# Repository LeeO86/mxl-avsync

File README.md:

# mxl-avsync

AV sync and latency measurement for MXL, iPhone and Android. Version 2.2 uses a
large QR code beside two always-opposite light fields that swap in a short
burst at each event (AVS3), plus independently decodable audio timecode. File,
live MXL and the phone apps share the signal and measuring core. The analyzer
reports audio/video offset and, with a suitable clock reference, latency.
Phone-clock latency is an estimate; its physical accuracy depends on the
phone's camera and microphone (calibrate once per phone).

Part of [mxl-stack](https://github.com/LeeO86/mxl-stack), a collection of open-source MXL media functions with Docker Compose and Kubernetes examples.

Get `ghcr.io/leeo86/mxl-avsync:2.2.0` or see the [AVsync project site](https://leeo86.github.io/mxl-avsync/)
for iOS TestFlight information. Upgrade compact-signal generator and receivers
together: the picture QR is now AVS4 (it also carries the test ID, the
generator name and the sender calibration); AVS2/AVS3 generators and receivers
cannot read it, and AVS4 receivers ignore them. Legacy signals remain supported.
[Signal and validation details](docs/qr-flash.md) · [Release notes](docs/release-notes-2.2.0.md).

**Status: measuring core, file tools, control plane, live MXL reader and writer, and the phone core.** The container image is `ghcr.io/leeo86/mxl-avsync`, user 1000:1000. `/metrics` exports every family from the first scrape, counters at 0. Latency gauges are not exported. `mxl-avsync` links libmxl when the package is found; `avsync-core` does not. `/readyz` is 200 when the process and HTTP service are up and, with NMOS registration configured, the node is listed in the Query API. The generator also requires its output flows to be created. Analyzer routes and signal are independent: `not_routed`, `waiting` and `no_signal` remain ready and are reported in `/statusz`, the input-state metric and the UI. The analyzer also writes a result picture flow, and the web UI polls `/api/v1/preview/input.jpg` and `/api/v1/preview/generated.jpg` once a second. Clock state comes from an optional ptp4l management socket (`AVSYNC_PTP_SOCKET`), otherwise the kernel (`adjtimex(2)`); `AVSYNC_PTP_STATUS_URL` is an explicit override. `/statusz`, `/api/v1/status`, the UI and metrics identify `sync_source` (`ptp4l`, `kernel` or `url`). See [clock reference and deployment requirements](docs/clock-reference.md) for socket permissions, PTP error reporting and NTP TAI setup. Latency and the index shifts are reported only when that clock is locked and the QR names the event. Latency is arrival vs the content timestamp; directly behind the generator it is the generator's own write timing (both essences committed about 20–25 ms early, so negative). The main value is the AV sync, which is what MXL consumers see. For an absolute latency (emission → arrival, never negative, with ± and the clock named), enter the source's emit offsets on the analyzer (`AVSYNC_SOURCE_EMIT_VIDEO_MS` / `AVSYNC_SOURCE_EMIT_AUDIO_MS`, copied from the generator's `/api/v1/status` `emit_offsets`), or route the generator's flows directly with a Query API configured (the analyzer then reads the generator's flow tag `urn:x-mxl:tag:avsync-emit-offset-ms/v1.0`); without either the latency is relative to the source timestamp. Alert rules: `deploy/prometheus/avsync-rules.yaml`; per-release bench over several paths: `tools/bench_paths.py`. `video_content_vs_grain_ms` and `audio_content_vs_grain_ms` compare that content time with the MXL grain timestamp even when the clock is unknown. This repo does not implement ST 2110, SRT, or SIP; those flows come from the sibling gateways. File-mode H.264 and G.711 are test aids. A real phone still needs a device. Read [SPECIFICATION.md](SPECIFICATION.md), [IMPLEMENTATION_PLAN.md](IMPLEMENTATION_PLAN.md) and [docs/test-matrix.md](docs/test-matrix.md).

## Build

```bash
cmake -S . -B build -G Ninja -DCMAKE_BUILD_TYPE=Release
cmake --build build
./build/avsync-core-tests
./tests/integration/api.sh
./tests/integration/file.sh
./tests/integration/stage2.sh
node --test mobile-app/src/display.test.mjs
```

Needs CMake, Ninja, a C++20 compiler and the FFmpeg development libraries (libavformat, libavcodec, libavutil, libswscale, libswresample).

```bash
./build/mxl-avsync generate --format 1080p50 --duration 60 --offset 0 --out test.mov
./build/mxl-avsync analyze test.mov --manifest test.mov.manifest.json
AVSYNC_ROLE=generator AVSYNC_STATE_DIR=/tmp/avsync ./build/mxl-avsync serve
```

## At a glance

- C++20; one dependency-free core (`avsync-core`) shared by the CLI, the media function and the later phone app.
- `av_offset_ms = audio − video`: **positive = audio late**.
- Grade: pass −5…+15 ms (green), warn −40…+60 ms (orange, EBU R37), fail outside (red).
- CLI: `mxl-avsync generate` (MOV + ProRes + PCM by default, with a JSON manifest), `analyze`, `validate`, `merge`.
- Media function: one image, `AVSYNC_ROLE=generator` or `analyzer`; one measuring point (video + audio) per analyzer.
- Analyzer outputs: REST, WebSocket, `/metrics`, the `avsync` widget, a result video flow for the multiviewer, Grafana alert rules.
- Metrics (prefix `mxl_avsync_`, every family from the first scrape): grade, AV offset (gauge, histogram), events by result, input state, skipped input grains, resyncs, absolute latency per essence (`latency_abs_ms` and `latency_abs_uncertainty_ms` gauges: median over the grade window, NaN without a value; `latency_abs_seconds` histogram), `emit_offset_mismatch_total`, audio correlation and level, clock and PTP state; generator frames written/late/missed, `generator_render_seconds` and `generator_render_budget_seconds`. Full list: SPECIFICATION §16. Alert rules: `deploy/prometheus/avsync-rules.yaml`.
- NMOS IS-04/IS-05 with nmos-cpp when the build has it. Node label equals `NMOS_LABEL` verbatim (or `HOST_ID` when unset); the device label appends the role. Sender/receiver labels stay unchanged. DNS-SD is off unless `NMOS_DNS_SD=true`. Transport is `urn:x-nmos:transport:mxl`. An IS-05 receiver PATCH needs `transport_params` (`mxl_domain_id` and `mxl_flow_id`) from the sender's `/active`. A PATCH that carries only `sender_id` increments the activation counter and leaves the analyzer `not_routed`. `/livez`, `/readyz`, `/metrics`. The image `HEALTHCHECK` calls `/livez` on `WEB_PORT` (default 8180).
- Paths in this repo: file round trips, file-mode H.264 and G.711 as test aids, and MXL flows. The ST 2110 hour run goes through mxl-st2110-gateway. SRT and SIP/G.711 live inputs arrive as MXL flows from the sibling gateways. Stage 2 uses those gateways and tests the matrix; there is no transport code here. Phone app (Expo, iOS and Android) in 2.0.

## Ports

| Port | Setting | Default |
| --- | --- | --- |
| Web UI, REST, probes, metrics, widgets | `WEB_PORT` | 8180 |
| NMOS Node and Connection APIs | `NMOS_PORT` | 3332 (+1 reserved) |

## Exit codes

0 `--help`/`--version` (and a CLI run that completed), 75 a port or another startup failure, 78 invalid configuration, 143 SIGTERM/SIGINT. CLI `analyze`: 2 when no event was found.

## Licence

MIT (`LICENSE`).

## Ready-to-play test clips

See [testfiles/README.md](testfiles/README.md) for eight verified AV-sync clips in MP4, MOV and MKV (720p to 4K), known offsets, manifests, analysis reports and regeneration commands.

Signal and Settings forms keep local drafts across status/JPEG polling, with an Unsaved changes indicator and Apply/Discard. Only successful Apply or explicit Discard adopts the server settings; failed saves and newer edits made during a save are retained.

## Audio timecode and optical burst

The default signal carries independently decodable audio timecode at 1200 baud.
At zero offset, each optical burst starts with the chirp. Choose 1 or 2 chirps/s
in Signal; 600 baud and legacy compatibility are also available. See
[the format, phone feedback, audio-only latency and tests](docs/audio-timecode.md).

## Test-picture labels

The Signal form's **Title** is the large caption below the sync scale;
**Subtitle** is smaller. For existing deployments the saved `source` field and
`AVSYNC_SOURCE` keep their names and values. The obsolete header `title` /
`AVSYNC_TITLE` remains accepted by the legacy API but is not a second title
control for AVS3. Both container and phone show the centered AVsync brand.

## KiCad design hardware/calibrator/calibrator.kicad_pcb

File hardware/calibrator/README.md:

# AV Sync calibrator board

<!-- SPDX-License-Identifier: CERN-OHL-P-2.0 -->

**Status: v0.3 proposal, in development. Not ordered, not built, not tested.**

A small giveaway board (66 × 22 mm) for the AVsync app. The phone powers it over a
USB-C to USB-C cable. **No cable comes with the board: the user needs their own.**
It calibrates:

- **camera mode**: a phone's camera against its microphone (LED flash + click together),
- **display mode**: a sending screen against its speaker (the board clicks when the
  screen pattern swaps).

The board picks the mode from its two light sensors. What the app must do is in
[`docs/calibrator.md`](../../docs/calibrator.md). The firmware can be updated over the
same USB-C socket from a PC (see [Update over USB](#update-over-usb)).

Black solder mask, ENIG finish: the orange parts of the AVsync logo (waveform and the
ring in the middle) are bare gold copper; the rest of the logo is white silkscreen. The
bottom has a QR code to <https://leeo86.github.io/mxl-avsync/>.

Schematic: [`renders/calibrator-schematic.pdf`](renders/calibrator-schematic.pdf)
(also [SVG](renders/calibrator.svg)). 3D view: [`renders/calibrator-3d.png`](renders/calibrator-3d.png).

## How it works (short)

- **MCU**: WCH CH32X035G8R6 (RISC-V, QSOP-28). It runs straight from the phone's 5 V
  (2–5.5 V; 3.0–5.3 V while USB is used); 10 Ω + 1 µF/100 nF filter spikes. No regulator,
  no crystal.
- **USB-C, 16 pins**: 5.1 kΩ on CC1/CC2 so the phone turns on 5 V. D+/D− go to the MCU
  (PC17/PC16) **only for firmware updates**. The firmware never turns the USB block or its
  D+ pull-up on, so a phone sees no USB device: no "accessory not supported" message and
  no audio route change.
- **BOOT button** SW1 (update mode): connects D+ (PC17) to VDD through 4.7 kΩ (R9). The ROM bootloader
  starts only at power-on and only if PC17 is high then (CH32X035 datasheet, pin note 8).
- **Flash and click**: white LED (PA4, ~12 mA) and buzzer transistor (PA5) are on the same
  port, so one register write starts both.
- **Light sensors**: two phototransistors feed comparator 3 (PA13 +, PA2 −, hysteresis on).
  It flips at the crossing point of a black/white swap. 22 kΩ + 1 nF per sensor
  (τ ≈ 22 µs) delays that point by only ~15 µs, the same on both sensors. The ADC reads the same nodes (PA0,
  PA2) for dark/light and to check that a flip is real. PB3 is the comparator output
  (used inside the firmware) and must stay unconnected.

### Choices on the update path

- **No 10 kΩ pull-down on D+.** It was meant to stop a dumb wall charger (which may put
  ~2.7 V on D+) from starting the bootloader. That case is harmless (the board just waits
  in update mode until unplugged; the phone use case is not affected, because a phone holds
  D+ low with its own 15 kΩ). A pull-down would also fight the button: with the PC's 15 kΩ
  in parallel, D+ would only reach about 2.8 V when the button is pressed, too close to the
  unknown input threshold. Without it D+ reaches ~3.8 V with a PC attached and 5 V without.
- **R9 = 4.7 kΩ** (as on community CH32X035 boards) limits the current into D+ to well under
  1 mA while the button is held.
- **No ESD part on D+/D−.** USB is only used for the occasional update, the MCU pins have
  their own protection, and an extra extended part costs $3.07 per order plus ~$0.04/board
  (+$0.35/board on the 10-board test). Revisit if boards fail.

## Mechanics: why holes through the board

The LED must touch the camera lens and the sensors must lie flat on the screen, but the
buzzer (3 mm) and the USB-C receptacle (3.2 mm) are much taller than an LED.

| Option | Cost per order | Result |
| --- | --- | --- |
| **Chosen: all parts on top, LED and sensors look down through holes, bottom side flat** | 0 extra; sensors cost ~$0.40/board more than normal ones | flat bottom touches lens and screen; one-side Economic PCBA |
| Two-sided assembly (LED + sensors on the bottom) | Standard PCBA: setup $51.12 instead of $8.18, stencil $16.42, fixtures $41 (100 pcs), $0.48/board minimum | ≈ +$1.00/board at 100 |
| LED and sensors on the top, board lies parts-down | 0 | does not lie flat: buzzer and plug are 3 mm tall |

Parts that make the hole idea work, all in JLC stock:

- **LED**: XINGLIGHT XL-3216UWC-FB, a white *reverse-mount* 1206 LED. Its lens sits in a
  2.1 × 1.7 mm cut-out and shines through the board. Lite-On LTW-C230DS (C575513) fits the
  same footprint as a second source.
- **Sensors**: Vishay VEMT2500X01, a *reverse-gullwing* phototransistor (visible + IR,
  ±15°). The body sits on top, the dome lens looks down through a 2.3 mm hole. With a
  **1.2 mm board** the lens ends flush with the bottom. VEMT2000X01 is the same package.
- **USB-C at the far end**: the cable plug is thicker than the board and sticks out
  ~0.5 mm below the bottom. It sits ~55 mm away from the LED and sensors, so the board tilts
  less than 1° and the LED end stays flat on the lens or screen.

Look and markings:

- **Logo** on both sides, from `assets/app-icon.svg`: on the top centred in the free area
  between the BOOT button and the USB-C, on the bottom in the middle of the board, 11 mm,
  beside the QR code; the short instructions sit at the LED/sensor end. Cyan and white strokes are silkscreen.
  The orange parts are copper with a solder-mask opening and no paste, so with ENIG they look
  gold. That copper has no net; keep-outs keep tracks and vias away from it. Like in the
  icon, the white dashed centre line and the white centre dot lie on top of the gold: the
  copper and its mask opening are cut away under them, because JLC removes silkscreen from
  bare copper. On the bottom the logo and QR are mirrored so they read right from below.
- **QR code** (bottom): `https://leeo86.github.io/mxl-avsync/`. Version 3-M, 0.45 mm modules
  (3× JLC's 0.153 mm minimum line), 4-module quiet zone, white silkscreen on black mask
  (normal polarity), no via holes inside. Checked: zxing-cpp decodes the bottom render, also
  at 1/3 size. Matrix: `scripts/qr_matrix.txt` (from `scripts/gen_qr.py`, needs `segno`).
- **Text**: one font; name 1.8–2.0 mm, sub-lines 1.0–1.2 mm, and JLC's minimum
  (1.0 mm / 0.153 mm stroke) for "not a toy", the licence (small, below the MCU); "BOOT" under SW1 (1.2 mm bold).
- **Alignment**: LED circle, `A`/`B`, the split line (on the top next to the LED and again
  behind the buzzer, so it is visible while the board lies face down) and a half-round notch
  in the board edge on the split line. Marks on both sides.
- iPhone camera bumps: the lens rings stand higher than the bump plate. The board rests on
  the ring of the lens under the LED circle; hold it lightly or tape it. The buzzer sits
  next to the LED (5 mm), sound port pointing at the LED, close to the rear microphone.
- No company name on the board. Ground copper on both layers stops light going sideways
  through the board; no vias at the optics end.

## BOM (JLCPCB/LCSC, live stock and prices checked 2026-11-08)

USD per part at the order quantity of 10 and 100 boards. Ext = extended part
($3.07 feeder fee per type, Economic PCBA).

| Ref | Part | LCSC | Lib | Qty | Stock | $ @10 | $ @100 |
| --- | --- | --- | --- | --- | --- | --- | --- |
| U1 | CH32X035G8R6, QSOP-28 | C49118551 | Ext | 1 | 800 | 0.4351 | 0.3304 |
| Q2, Q3 | VEMT2500X01 phototransistor, reverse gullwing | C3210911 | Ext | 2 | 782 | 0.3141 | 0.2306 |
| BZ1 | MLT-8530 magnetic buzzer 8.5 × 8.5 × 3 mm | C94599 | Ext | 1 | 137,398 | 0.2015 | 0.158 |
| J1 | TYPE-C 16P receptacle (SHOU HAN), USB 2.0 | C393939 | Ext | 1 | 366,678 | 0.0691 | 0.0553 |
| D1 | XL-3216UWC-FB white LED, reverse mount | C3646935 | Ext | 1 | 111,067 | 0.0164 | 0.0164 |
| SW1 | TS-1187A tact switch 5.1 × 5.1 mm (update) | C318884 | Basic | 1 | 871,253 | 0.0207 | 0.0207 |
| Q1 | S8050 NPN, SOT-23 | C2146 | Basic | 1 | 1.45 M | 0.0141 | 0.0141 |
| D2 | 1N4148WS, SOD-323 | C2128 | Basic | 1 | 2.8 M | 0.011 | 0.011 |
| C1 | 10 µF 25 V 0805 | C15850 | Basic | 1 | 8.7 M | 0.0359 | 0.0359 |
| C2 | 1 µF 0402 | C52923 | Basic | 1 | 11.5 M | 0.0058 | 0.0058 |
| C3 | 100 nF 0402 | C1525 | Basic | 1 | 34.2 M | 0.0031 | 0.0031 |
| C4, C5 | 1 nF 0402 | C1523 | Basic | 2 | 2.3 M | 0.0038 | 0.0038 |
| R1, R2 | 5.1 kΩ 0402 | C25905 | Basic | 2 | 4.5 M | 0.0023 | 0.0023 |
| R3 | 10 Ω 0402 | C25077 | Basic | 1 | 3.6 M | 0.001 | 0.001 |
| R4 | 150 Ω 0603 | C22808 | Basic | 1 | 1.3 M | 0.0015 | 0.0015 |
| R5 | 1 kΩ 0402 | C11702 | Basic | 1 | 33.7 M | 0.0013 | 0.0013 |
| R6 | 100 kΩ 0402 | C25741 | Basic | 1 | 8.8 M | 0.0012 | 0.0012 |
| R7, R8 | 22 kΩ 0402 | C25768 | Basic | 2 | 1.0 M | 0.0012 | 0.0012 |
| R9 | 4.7 kΩ 0402 | C25900 | Basic | 1 | 15.7 M | 0.0017 | 0.0017 |

**Parts per board: $1.80 @10, $1.16 @100.** Stock covers the 10 + 100 boards (U1: 800,
sensors: 782 for 220 needed). Reserve them in the JLC parts library before ordering.

## Cost (both orders, CHF, everything included, no cables)

Assumptions: Economic PCBA fees from the JLC price page (setup $8.18, stencil $1.53,
5 extended types × $3.07, 95 joints × $0.0016, Confirm Parts Placement $0.45); PCB 2-layer
66 × 22 mm, 1.2 mm, **ENIG, black mask** [estimate: $21 for 10, $42 for 100; JLC's PCB price
only comes from their JavaScript calculator]; DHL $20 / $30 [estimate]; 1 USD = 0.80 CHF;
Swiss import VAT 8.1 % (only when ≥ CHF 5) + DHL clearance CHF 11.50 + 3 %.

| | Test, 10 boards | Run, 100 boards |
| --- | --- | --- |
| Parts | $18.0 | $116.0 |
| PCBA fees | $27.0 | $40.7 |
| PCB with ENIG + black | ~$21 | ~$42 |
| DHL | ~$20 | ~$30 |
| Subtotal | $86 → CHF 69 | $229 → CHF 183 |
| VAT 8.1 % + DHL clearance | CHF 5.6 + 11.7 | CHF 14.8 + 11.9 |
| **Total** | **≈ CHF 86 (CHF 8.60/board)** | **≈ CHF 210 (CHF 2.10/board)** |

**Both orders: ≈ CHF 296**, just under the CHF 300 budget. No programmer is needed (update
over USB-C). No cables are included. Ways to get more margin: JLC Global Standard Direct
instead of DHL (−CHF 10–20), or HASL instead of ENIG on the test batch (−~CHF 15; also stays
under the VAT limit). Run the real JLC quote with `fab/calibrator-gerbers.zip` before ordering.

## Update over USB

The CH32X035 has a USB bootloader in ROM, so the board cannot be bricked and needs no
programmer.

1. Unplug the board. Hold the **BOOT** button (SW1).
2. Plug the board into a PC (USB-C to USB-C, or USB-A to C). Release after about a second.
3. The board shows up as a WCH ISP device. Flash with an open tool:
   - [`wchisp`](https://github.com/ch32-rs/wchisp) (Rust, GPL-2.0): `wchisp flash firmware/build/calibrator.bin`
   - or `chprog.py` from [wagiminator/MCU-Flash-Tools](https://github.com/wagiminator/MCU-Flash-Tools) (MIT).
4. Unplug and plug in again: the new firmware runs.

A **blank chip** (as delivered by JLC) always starts the bootloader, so the first flash
needs no button. Linux needs a udev rule for the WCH device; see the
[firmware README](firmware/README.md). In normal use (no button) the phone never sees a
USB device.

## Files

| Path | What |
| --- | --- |
| `calibrator.kicad_pro/.kicad_sch/.kicad_pcb` | KiCad 9 project |
| `calibrator.kicad_sym` | custom CH32X035G8R6 symbol with pins grouped by use |
| `calibrator.pretty/` | custom footprints (buzzer, reverse LED, reverse-gullwing sensor) |
| `3d/` | simple box 3D models for the renders (KiCad 9's image has none for some parts; renders only, not used for assembly) |
| `fab/calibrator-gerbers.zip` | gerbers + drill for JLCPCB (order **1.2 mm**, **ENIG**, **black** mask, white silk) |
| `fab/calibrator-bom-jlc.csv`, `fab/calibrator-cpl-jlc.csv` | JLC BOM and pick-and-place files |
| `renders/` | PNG renders, schematic PDF/SVG |
| `scripts/` | generators: `design.py` (parts, nets, placement) → schematic (`gen_sch.py`, drawn in code), board (`gen_pcb.py`), fab files; `check_netlist.py` checks the drawn schematic against `design.py` |
| `firmware/` | CH32X035 firmware + host tests ([README](firmware/README.md)) |

### Rebuild

Needs docker only (pinned images `kicad/kicad:9.0.9-full`, `ghcr.io/freerouting/freerouting:2.1.0`).

```sh
scripts/build.sh   # footprints, schematic + netlist check, placement, autoroute, ground stitching, ERC, DRC
scripts/fab.sh     # gerbers, drill, BOM, CPL, renders, schematic PDF/SVG
```

The autorouter does not give the same tracks every run; the committed board is the
checked one.

### Checks

- ERC: 0 violations. Netlist check: the schematic wires give exactly the nets in `design.py`.
- DRC: 0 violations, 0 unconnected (JLC rules: 0.15 mm track/space, 0.3/0.6 mm vias,
  0.3 mm copper to board edge).
- Footprints match the datasheets (U1: QSOP-28 3.9 × 9.9 mm, 0.635 mm pitch, pin 1 top left;
  the USB-C uses KiCad's HRO TYPE-C-31-M-12 footprint, same pad layout as the SHOU HAN
  C393939 drawing).
- CPL rotations: JLC's 0° is the orientation of its own footprint for each part, which is
  not always KiCad's. `scripts/jlc_files.py` adds the known offsets for the stock footprints
  (QSOP-28 +270°, SOT-23 −90°, HRO USB-C +180°; values from the community list of JLC
  corrections, e.g. matthewlai/JLCKicadTools). Custom footprints (buzzer, reverse LED,
  sensors) and the button keep KiCad's rotation. Still check every part in JLC's placement
  preview before ordering (or use "Confirm Parts Placement"); JLC also places by the pin-1
  and polarity marks in the silkscreen.

## Risks and open points

1. **Phone powers the board?** A sink with 5.1 kΩ Rd is the standard USB-C way to ask for
   5 V. iPhone 15+ and most Android phones supply it. To test with real phones, including
   that no "accessory" message appears with D+/D− wired to the MCU.
2. **Bootloader entry**: R9/SW1 values follow community boards, not a WCH document; one
   user reports an "unknown device" when powered only from USB-C. Test on the first board.
3. **Comparator interrupt path** (comparator 3 → PB3 → EXTI) and the ADC/clock register
   setup are written from the datasheet, ch32fun and WCH EVT, not tested on hardware.
4. **Buzzer delay** from coil-on to sound is unknown (expect 0.05–0.3 ms). Measure once.
5. **Sensor signal** on dim screens (22 kΩ load) and room light entering the clear sensor
   bodies from above (both sensors alike, mostly cancels).
6. **LED fit**: the reverse LED lens (1.86 × 1.4 mm) has only ~0.1 mm room in the cut-out.
7. **Stock**: U1 800 and sensors 782 at JLC; enough for 110 boards, not for many more.
8. **VDD with USB**: the datasheet allows 3.0–5.3 V while USB runs; a PC port at the top of
   the USB range (5.25 V) is just inside.

## Licence

- **Board** (KiCad project, footprints, 3D models, scripts, fab files, renders and the logo
  artwork on the board): **CERN-OHL-P-2.0**, see
  [`LICENSE-CERN-OHL-P-2.0.txt`](LICENSE-CERN-OHL-P-2.0.txt).
  `SPDX-License-Identifier: CERN-OHL-P-2.0`. It is printed small on the top silkscreen.
  CERN-OHL-S-2.0 (share-alike: changed boards must stay open) would be the alternative.
- **Firmware** (`firmware/`): MIT, like the rest of the repository. Vendored register
  definitions come from ch32fun (MIT); see [`firmware/vendor/README.md`](firmware/vendor/README.md).

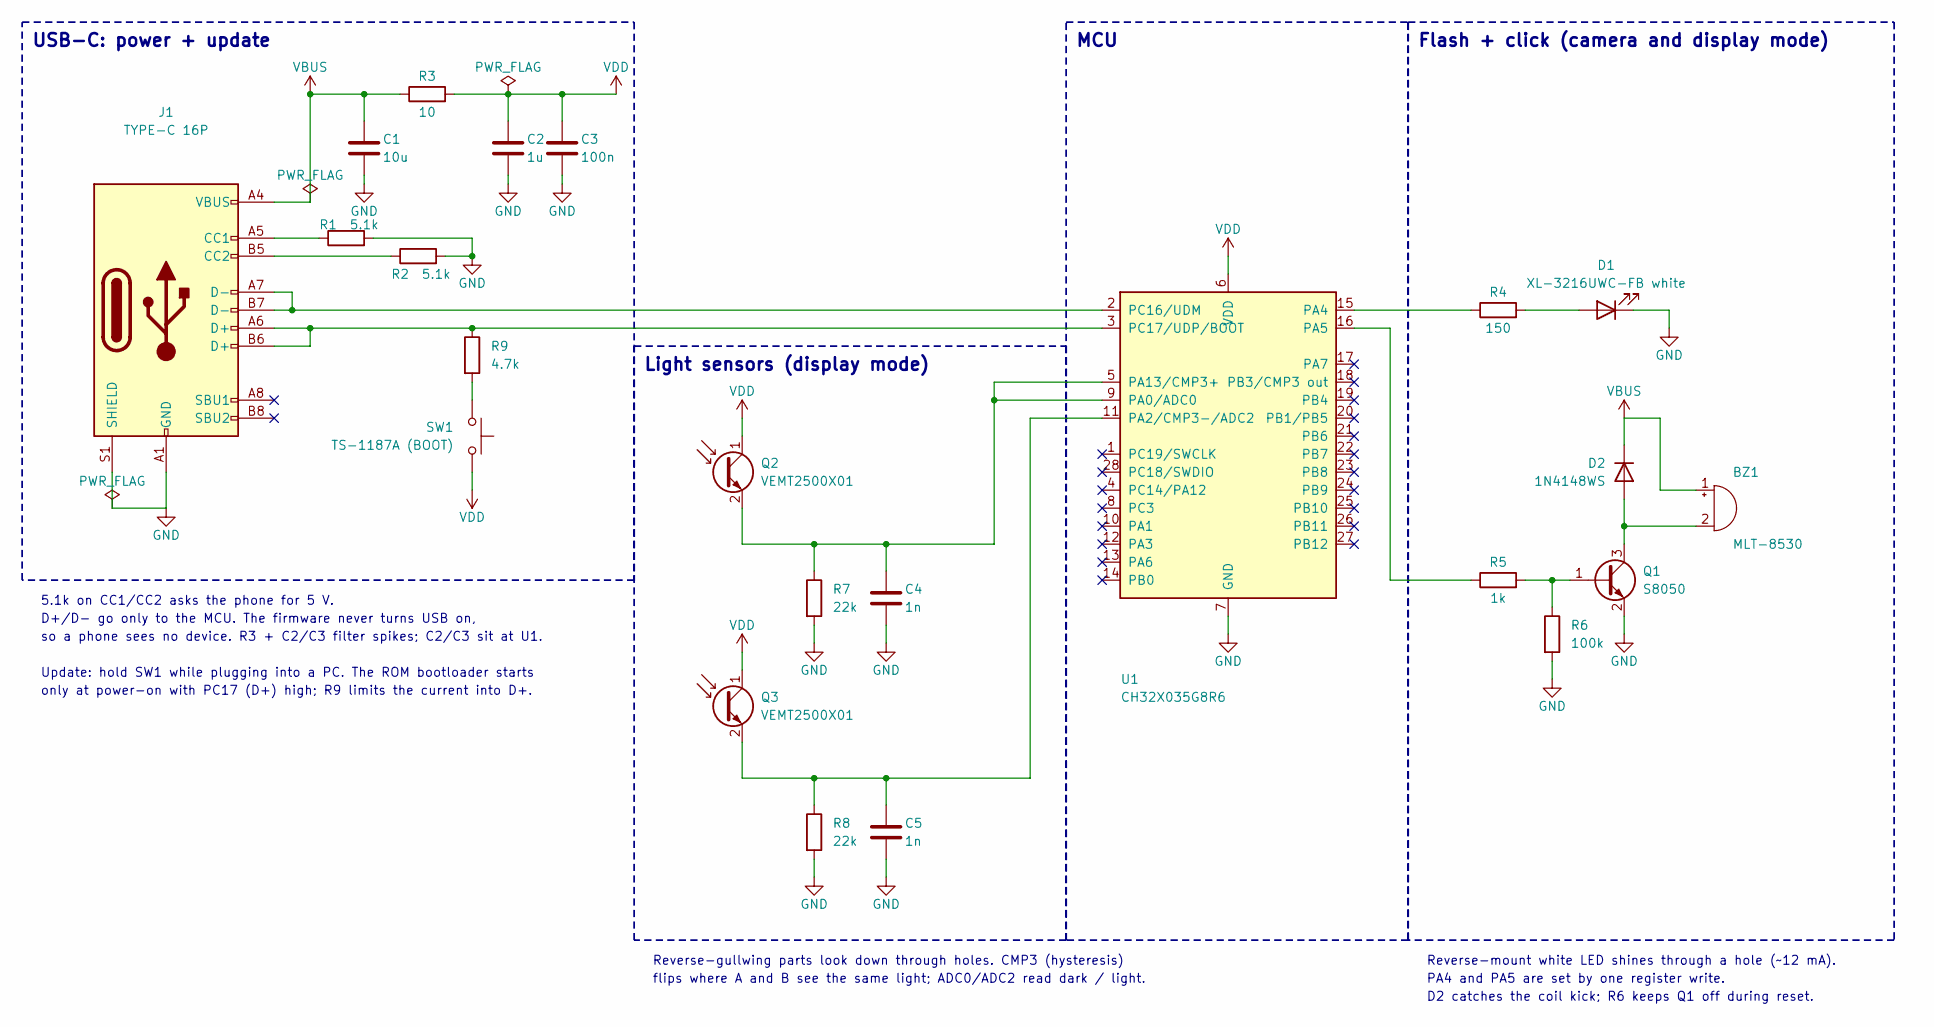
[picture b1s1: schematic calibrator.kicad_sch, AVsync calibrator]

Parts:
BZ1: MLT-8530; Buzzer_MLT-8530; LCSC C94599
C1: 10u; C_0805_2012Metric; LCSC C15850
C2: 1u; C_0402_1005Metric; LCSC C52923
C3: 100n; C_0402_1005Metric; LCSC C1525
C4, C5: 1n; C_0402_1005Metric; LCSC C1523
D1: XL-3216UWC-FB white; LED_1206_ReverseMount_XL-3216UWC-FB; LCSC C3646935
D2: 1N4148WS; D_SOD-323; LCSC C2128
J1: TYPE-C 16P; USB_C_Receptacle_HRO_TYPE-C-31-M-12; LCSC C393939
Q1: S8050; SOT-23; LCSC C2146
Q2, Q3: VEMT2500X01; Vishay_VEMT2500X01_ReverseGullwing; LCSC C3210911
R1, R2: 5.1k; R_0402_1005Metric; LCSC C25905
R3: 10; R_0402_1005Metric; LCSC C25077
R4: 150; R_0603_1608Metric; LCSC C22808
R5: 1k; R_0402_1005Metric; LCSC C11702
R6: 100k; R_0402_1005Metric; LCSC C25741
R7, R8: 22k; R_0402_1005Metric; LCSC C25768
R9: 4.7k; R_0402_1005Metric; LCSC C25900
SW1: TS-1187A (BOOT); SW_Push_1P1T_XKB_TS-1187A; LCSC C318884
U1: CH32X035G8R6; QSOP-28_3.9x9.9mm_P0.635mm; LCSC C49118551

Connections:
BOOT: R9.2, SW1.1
BUZ_B: Q1.1 (B), R5.2, R6.1
BUZ_DRV: R5.1, U1.16 (PA5)
BUZ_N: BZ1.2 (-), D2.2 (A), Q1.3 (C)
CC1: J1.A5 (CC1), R1.1
CC2: J1.B5 (CC2), R2.1
DM: J1.A7 (D-), J1.B7 (D-), U1.2 (PC16/UDM)
DP: J1.A6 (D+), J1.B6 (D+), R9.1, U1.3 (PC17/UDP/BOOT)
GND: C1.2, C2.2, C3.2, C4.2, C5.2, D1.1 (K), J1.A1 (GND), J1.A12 (GND), J1.B1 (GND), J1.B12 (GND), J1.S1 (SHIELD), Q1.2 (E), R1.2, R2.2, R6.2, R7.2, R8.2, U1.7 (GND)
LED_A: D1.2 (A), R4.2
LED_DRV: R4.1, U1.15 (PA4)
SENS_A: C4.1, Q2.2 (E), R7.1, U1.5 (PA13/CMP3+), U1.9 (PA0/ADC0)
SENS_B: C5.1, Q3.2 (E), R8.1, U1.11 (PA2/CMP3-/ADC2)
VBUS: BZ1.1 (+), C1.1, D2.1 (K), J1.A4 (VBUS), J1.A9 (VBUS), J1.B4 (VBUS), J1.B9 (VBUS), R3.1
VDD: C2.1, C3.1, Q2.1 (C), Q3.1 (C), R3.2, SW1.2, U1.6 (VDD)

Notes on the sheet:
USB-C: power + update
Light sensors (display mode)
MCU
Flash + click (camera and display mode)
5.1k on CC1/CC2 asks the phone for 5 V.
D+/D- go only to the MCU. The firmware never turns USB on,
so a phone sees no device. R3 + C2/C3 filter spikes; C2/C3 sit at U1.
Update: hold SW1 while plugging into a PC. The ROM bootloader starts
only at power-on with PC17 (D+) high; R9 limits the current into D+.
Reverse-gullwing parts look down through holes. CMP3 (hysteresis)
flips where A and B see the same light; ADC0/ADC2 read dark / light.
Reverse-mount white LED shines through a hole (~12 mA).
PA4 and PA5 are set by one register write.
D2 catches the coil kick; R6 keeps Q1 off during reset.

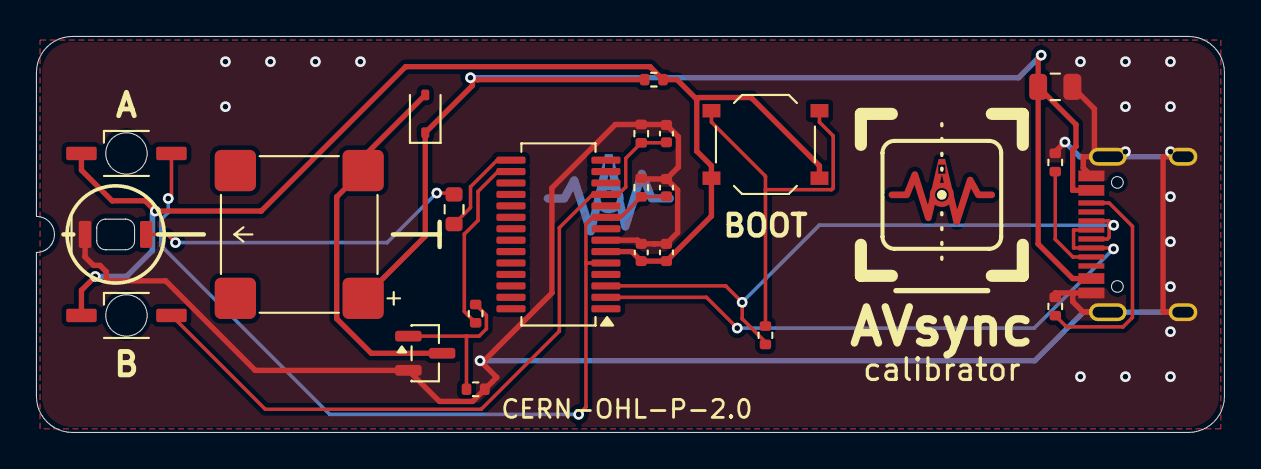
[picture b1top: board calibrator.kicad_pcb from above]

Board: 2 copper layers, 66.0 x 22.0 mm, 23 parts (0 on the bottom side), 15 nets.

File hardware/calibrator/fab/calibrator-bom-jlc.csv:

Comment,Designator,Footprint,LCSC Part #
MLT-8530,BZ1,Buzzer_MLT-8530,C94599
10u,C1,C_0805_2012Metric,C15850
1u,C2,C_0402_1005Metric,C52923
100n,C3,C_0402_1005Metric,C1525
1n,"C4,C5",C_0402_1005Metric,C1523
XL-3216UWC-FB white,D1,LED_1206_ReverseMount_XL-3216UWC-FB,C3646935
1N4148WS,D2,D_SOD-323,C2128
TYPE-C 16P,J1,USB_C_Receptacle_HRO_TYPE-C-31-M-12,C393939
S8050,Q1,SOT-23,C2146
VEMT2500X01,"Q2,Q3",Vishay_VEMT2500X01_ReverseGullwing,C3210911
5.1k,"R1,R2",R_0402_1005Metric,C25905
10,R3,R_0402_1005Metric,C25077
150,R4,R_0603_1608Metric,C22808
1k,R5,R_0402_1005Metric,C11702
100k,R6,R_0402_1005Metric,C25741
22k,"R7,R8",R_0402_1005Metric,C25768
4.7k,R9,R_0402_1005Metric,C25900
TS-1187A (BOOT),SW1,SW_Push_1P1T_XKB_TS-1187A,C318884
CH32X035G8R6,U1,QSOP-28_3.9x9.9mm_P0.635mm,C49118551
